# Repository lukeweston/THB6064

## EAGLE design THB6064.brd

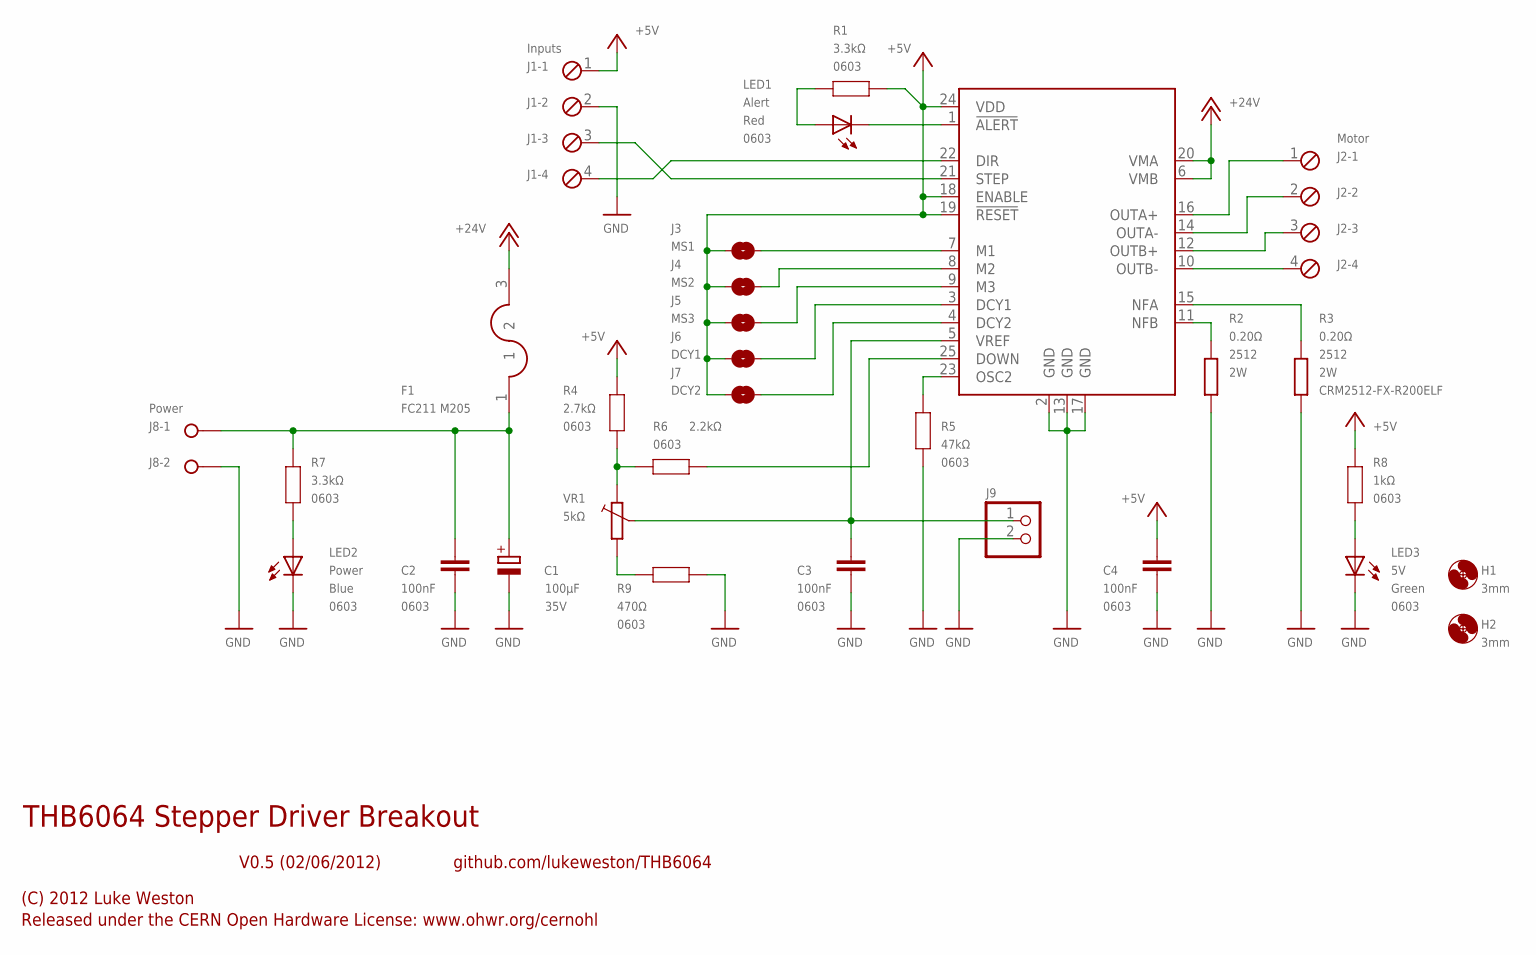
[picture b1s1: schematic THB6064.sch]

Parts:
C1: 100µF; E3,5-8; VOLTAGE 35V
C2, C3, C4: 100nF; 0603
F1: FC211 M205; FUSE_5MM
H1, H2: 3mm; 3,0
IC1: THB6064; ZIP25
J1: Inputs; 4POL254
J2: Motor; 4POL254
J3: MS1; SJ
J4: MS2; SJ
J5: MS3; SJ
J6: DCY1; SJ
J7: DCY2; SJ
J8: Power; W237-132
J9: PINHD-1X2; 1X02
LED1: Alert; LED-0603
LED2: Power; LED-0603
LED3: 5V; LED-0603
R1, R7: 3.3kΩ; 0603
R2, R3: 0.20Ω; R2512
R4: 2.7kΩ; 0603
R5: 47kΩ; 0603
R6: 2.2kΩ; 0603
R8: 1kΩ; 0603
R9: 470Ω; 0603
VR1: 5kΩ; CT6

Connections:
+5V: C4.1, IC1.18 (ENABLE), IC1.19 (!RESET), IC1.24 (VDD), J1.1, J3.1, J4.1, J5.1, J6.1, J7.1, R1.2, R4.2, R8.2
+12V: F1.3 (2), IC1.6 (VMB), IC1.20 (VMA)
DIR: IC1.22 (DIR), J1.4
GND: C1.-, C2.2, C3.2, C4.2, IC1.2 (GND), IC1.13 (GND), IC1.17 (GND), J1.2, J8.2, J9.2, LED2.C, LED3.C, R2.1, R3.1, R5.1, R9.1
MA+: IC1.16 (OUTA+), J2.1
MA-: IC1.14 (OUTA-), J2.2
MB+: IC1.12 (OUTB+), J2.3
MB-: IC1.10 (OUTB-), J2.4
unnamed: LED2.A, R7.1
unnamed: LED3.A, R8.1
unnamed: C1.+, C2.1, F1.1, J8.1, R7.2
unnamed: C3.1, IC1.5 (VREF), J9.1, VR1.S
unnamed: IC1.25 (DOWN), R6.1
unnamed: R4.1, R6.2, VR1.E
unnamed: IC1.1 (!ALERT), LED1.C
unnamed: LED1.A, R1.1
unnamed: R9.2, VR1.A
unnamed: IC1.23 (OSC2), R5.2
unnamed: IC1.11 (NFB), R2.2
unnamed: IC1.15 (NFA), R3.2
unnamed: IC1.4 (DCY2), J7.2
unnamed: IC1.3 (DCY1), J6.2
unnamed: IC1.9 (M3), J5.2
unnamed: IC1.8 (M2), J4.2
unnamed: IC1.7 (M1), J3.2
STEP: IC1.21 (STEP), J1.3

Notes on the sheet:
THB6064 Stepper Driver Breakout
V0.5 (02/06/2012)
(C) 2012 Luke Weston
Released under the CERN Open Hardware License: www.ohwr.org/cernohl
github.com/lukeweston/THB6064

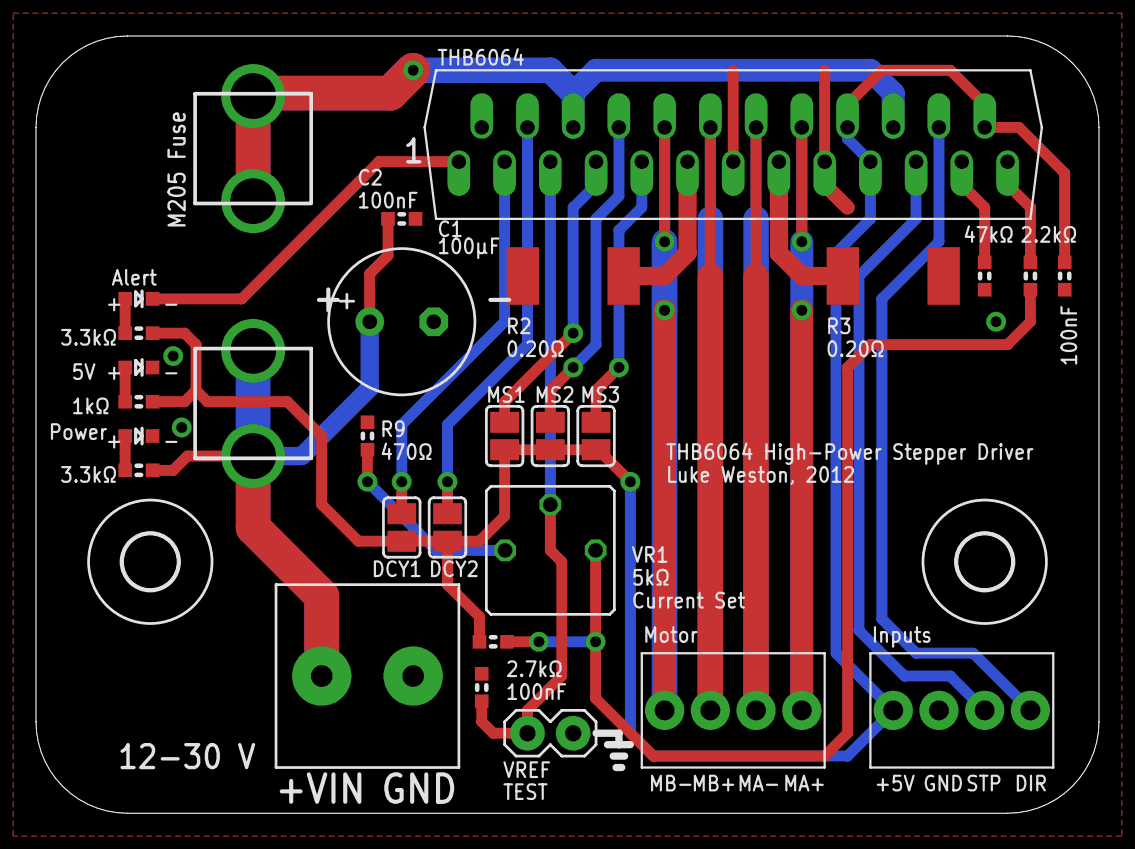
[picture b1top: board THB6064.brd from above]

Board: 2 copper layers, 59.1 x 43.2 mm, 30 parts (0 on the bottom side), 26 nets.
